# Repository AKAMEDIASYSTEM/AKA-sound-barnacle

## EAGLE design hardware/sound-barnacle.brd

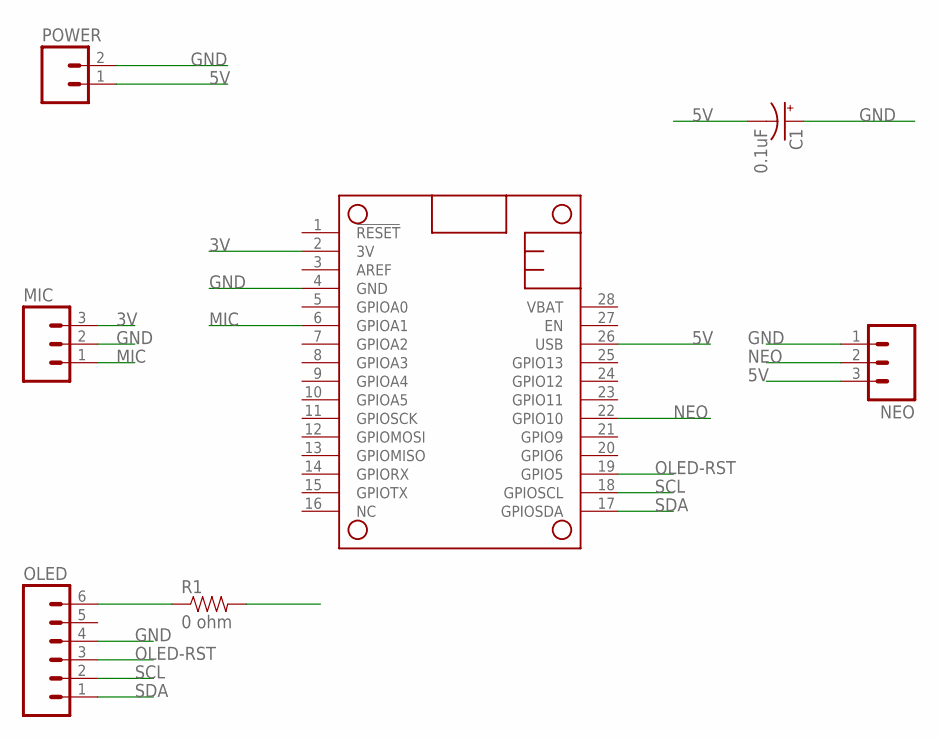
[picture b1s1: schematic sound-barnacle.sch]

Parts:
C1: 0.1uF; B45181B
MIC: M03LOCK_LONGPADS; 1X03_LOCK_LONGPADS
MS1: FEATHERWING
NEO: M03LOCK_LONGPADS; 1X03_LOCK_LONGPADS
OLED: M06LOCK_LONGPADS; 1X06_LOCK_LONGPADS
POWER: M02LOCK_LONGPADS; 1X02_LOCK_LONGPADS
R1: 0 ohm; AXIAL-0.3

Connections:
3V: MIC.3, MS1.2 (3V), R1.P$2 (2)
5V: C1.-, MS1.26 (USB), NEO.3, POWER.1
GND: C1.+, MIC.2, MS1.4 (GND), NEO.1, OLED.4, POWER.2
MIC: MIC.1, MS1.6 (GPIOA1)
unnamed: OLED.6, R1.P$1 (1)
NEO: MS1.22 (GPIO10), NEO.2
OLED-RST: MS1.19 (GPIO5), OLED.3
SCL: MS1.18 (GPIOSCL), OLED.2
SDA: MS1.17 (GPIOSDA), OLED.1

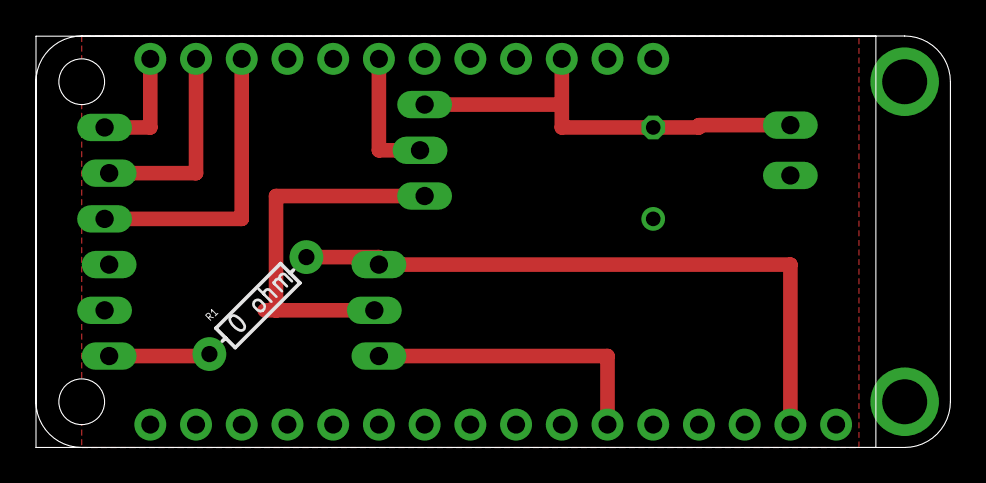
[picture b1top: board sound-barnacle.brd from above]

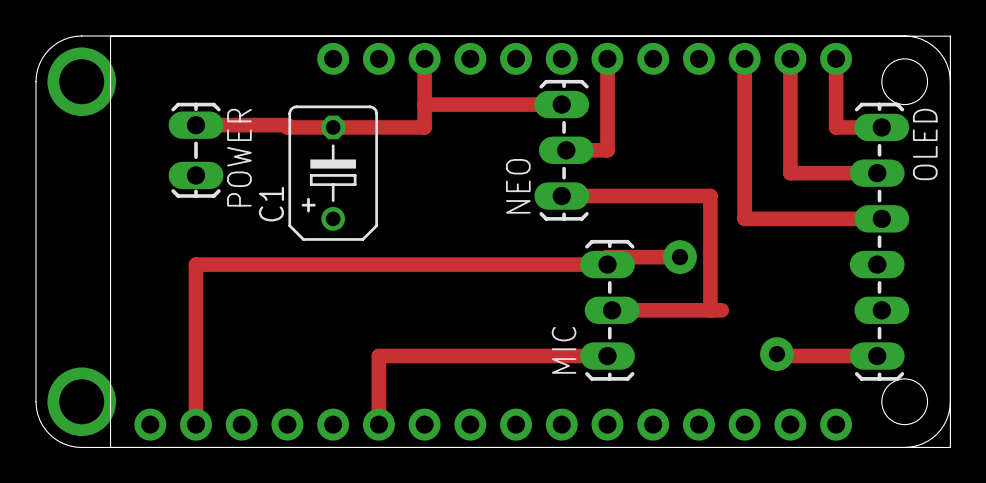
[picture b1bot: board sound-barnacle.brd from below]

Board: 2 copper layers, 50.8 x 22.9 mm, 7 parts (6 on the bottom side), 9 nets.

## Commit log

2016-03-26 fixed some issues that prevented it from running independently - ready for longer-term testing
2016-03-26 added hw files and changed structure
2016-04-16 modified for 60-pixel rgbw ring
2017-12-01 fixing longstanding server formatting typo

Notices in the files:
parts and their libraries:
SparkFun-Connectors: Licensing: Creative Commons ShareAlike 4.0 International - https://creativecommons.org/licenses/by-sa/4.0
